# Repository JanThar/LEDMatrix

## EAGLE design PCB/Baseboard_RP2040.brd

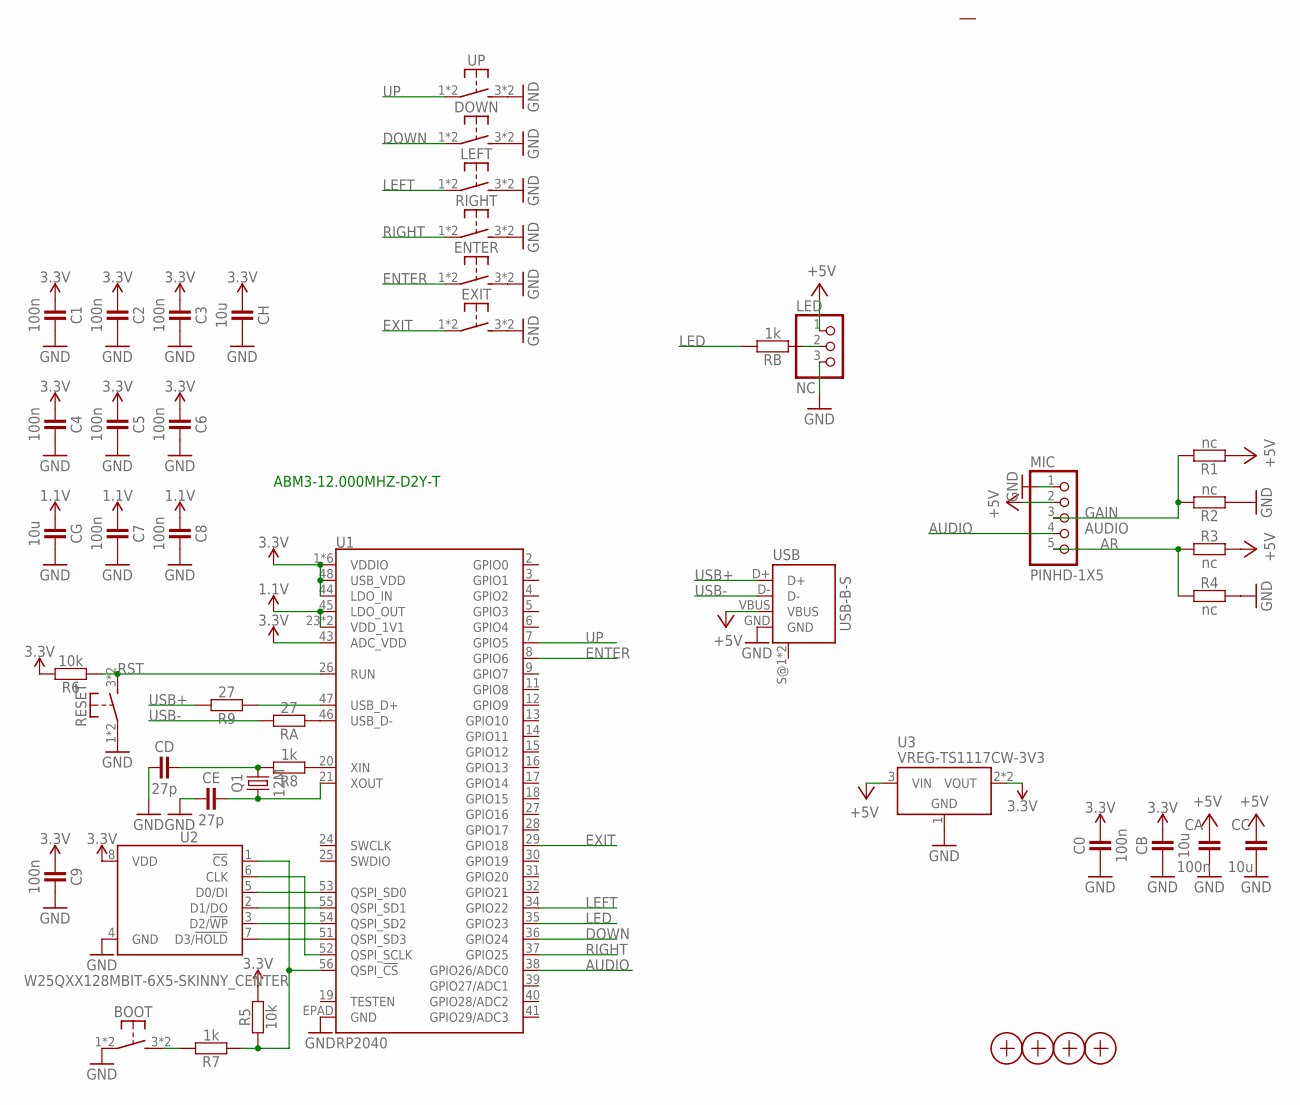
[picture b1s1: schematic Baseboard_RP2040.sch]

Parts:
BOOT: SW-TACTILE-6X6_SMD; SW6X6_SMD
C0, C1, C2, C3, C4, C5, C6, C7, C8, C9: 100n; C0603
CA: 100n; C0603
CB: 10u; C0603
CC: 10u; C0603
CD: 27p; C0603
CE: 27p; C0603
CG: 10u; C0603
CH: 10u; C0603
DOWN: SW-TACTILE-6X6_SMD; SW6X6_SMD
ENTER: SW-TACTILE-6X6_SMD; SW6X6_SMD
EXIT: SW-TACTILE-6X6_SMD; SW6X6_SMD
LED: NC; 1X03
LEFT: SW-TACTILE-6X6_SMD; SW6X6_SMD
MIC: PINHD-1X5; 1X05
Q1: 12M; CRYSTAL_CC2
R1, R2, R3, R4: nc; C0603
R5, R6: 10k; C0603
R7, R8: 1k; C0603
R9: 27; C0603
RA: 27; C0603
RB: 1k; C0603
RESET: SW-TACTILE-6X6_SMD; SW6X6_SMD
RIGHT: SW-TACTILE-6X6_SMD; SW6X6_SMD
U1: RP2040; QFN-56
U2: W25QXX128MBIT-6X5-SKINNY_CENTER; WSON-8-6X5-SKINNY_CENTERPAD
U3: VREG-TS1117CW-3V3; SOT223
UP: SW-TACTILE-6X6_SMD; SW6X6_SMD
USB: USB-B-S
X1, X2, X3, X4: PASSER-07; PASSER_07MM

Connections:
1.1V: C7.1, C8.1, CG.1, U1.23 (VDD_1V1), U1.45 (LDO_OUT), U1.50 (VDD_1V1)
3.3V: C0.2, C1.1, C2.1, C3.1, C4.1, C5.1, C6.1, C9.1, CB.2, CH.1, R5.2, R6.2, U1.1 (VDDIO), U1.10 (VDDIO), U1.22 (VDDIO), U1.33 (VDDIO), U1.42 (VDDIO), U1.43 (ADC_VDD), U1.44 (LDO_IN), U1.48 (USB_VDD), U1.49 (VDDIO), U2.8 (VDD), U3.2 (VOUT), U3.4 (VOUT)
+5V: CA.2, CC.2, LED.1, MIC.2, R1.1, R3.2, U3.3 (VIN), USB.VBUS
AR: MIC.5, R3.1, R4.1
AUDIO: MIC.4, U1.38 (GPIO26/ADC0)
DOWN: DOWN.1, DOWN.2 (P1), U1.36 (GPIO24)
ENTER: ENTER.1, ENTER.2 (P1), U1.8 (GPIO6)
EXIT: EXIT.1, EXIT.2 (P1), U1.29 (GPIO18)
GAIN: MIC.3, R1.2, R2.2
GND: BOOT.1, BOOT.2 (P1), C0.1, C1.2, C2.2, C3.2, C4.2, C5.2, C6.2, C7.2, C8.2, C9.2, CA.1, CB.1, CC.1, CD.1, CE.1, CG.2, CH.2, DOWN.3 (S1), DOWN.4 (S1), ENTER.3 (S1), ENTER.4 (S1), EXIT.3 (S1), EXIT.4 (S1), LED.3, LEFT.3 (S1), LEFT.4 (S1), MIC.1, R2.1, R4.2, RESET.1, RESET.2 (P1), RIGHT.3 (S1), RIGHT.4 (S1), U1.EPAD (GND), U2.4 (GND), U3.1 (GND), UP.3 (S1), UP.4 (S1), USB.GND
LED: RB.2, U1.35 (GPIO23)
LEFT: LEFT.1, LEFT.2 (P1), U1.34 (GPIO22)
unnamed: LED.2, RB.1
unnamed: U1.53 (QSPI_SD0), U2.5 (D0/DI)
unnamed: U1.55 (QSPI_SD1), U2.2 (D1/DO)
unnamed: U1.54 (QSPI_SD2), U2.3 (D2/!WP!)
unnamed: U1.51 (QSPI_SD3), U2.7 (D3/!HOLD!)
unnamed: U1.52 (QSPI_SCLK), U2.6 (CLK)
unnamed: R5.1, R7.1, U1.56 (QSPI_!CS!), U2.1 (!CS!)
unnamed: BOOT.3 (S1), BOOT.4 (S1), R7.2
unnamed: R8.1, U1.20 (XIN)
unnamed: CD.2, Q1.2, R8.2
unnamed: CE.2, Q1.1, U1.21 (XOUT)
unnamed: R9.1, U1.47 (USB_D+)
unnamed: RA.1, U1.46 (USB_D-)
RIGHT: RIGHT.1, RIGHT.2 (P1), U1.37 (GPIO25)
RST: R6.1, RESET.3 (S1), RESET.4 (S1), U1.26 (RUN)
UP: U1.7 (GPIO5), UP.1, UP.2 (P1)
USB+: R9.2, USB.D+
USB-: RA.2, USB.D-

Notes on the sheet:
ABM3-12.000MHZ-D2Y-T

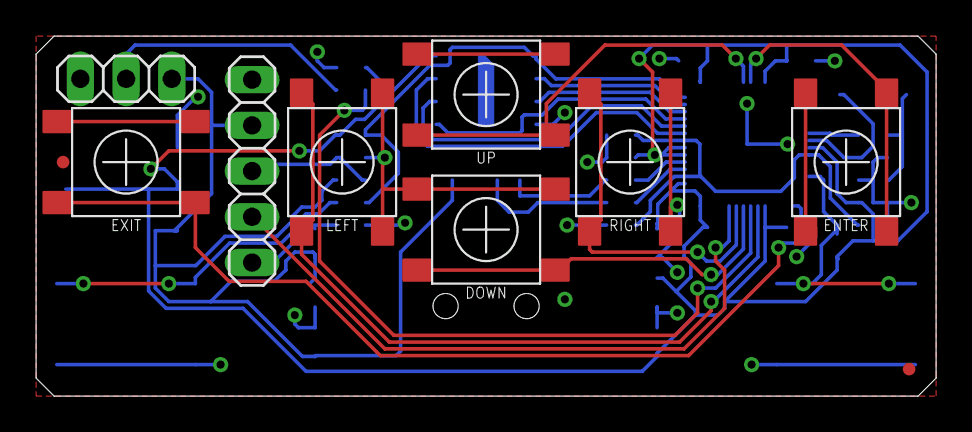
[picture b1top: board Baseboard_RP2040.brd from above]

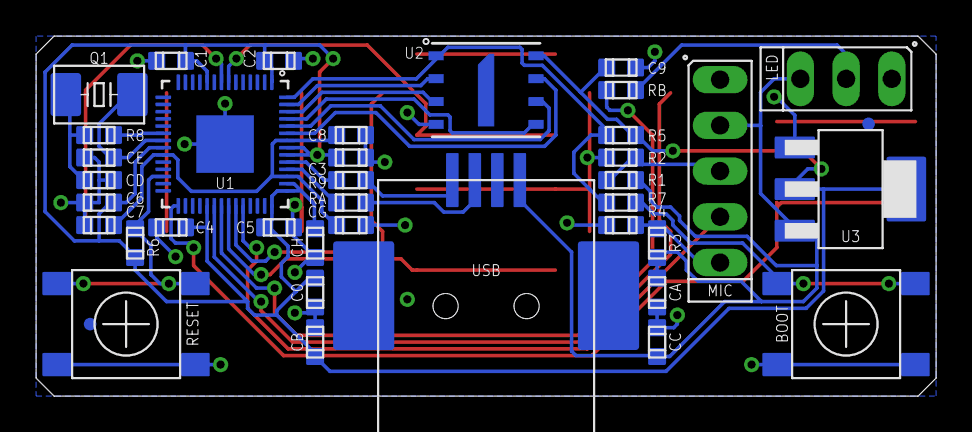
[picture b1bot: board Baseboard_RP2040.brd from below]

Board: 2 copper layers, 50.0 x 20.0 mm, 47 parts (37 on the bottom side), 30 nets.

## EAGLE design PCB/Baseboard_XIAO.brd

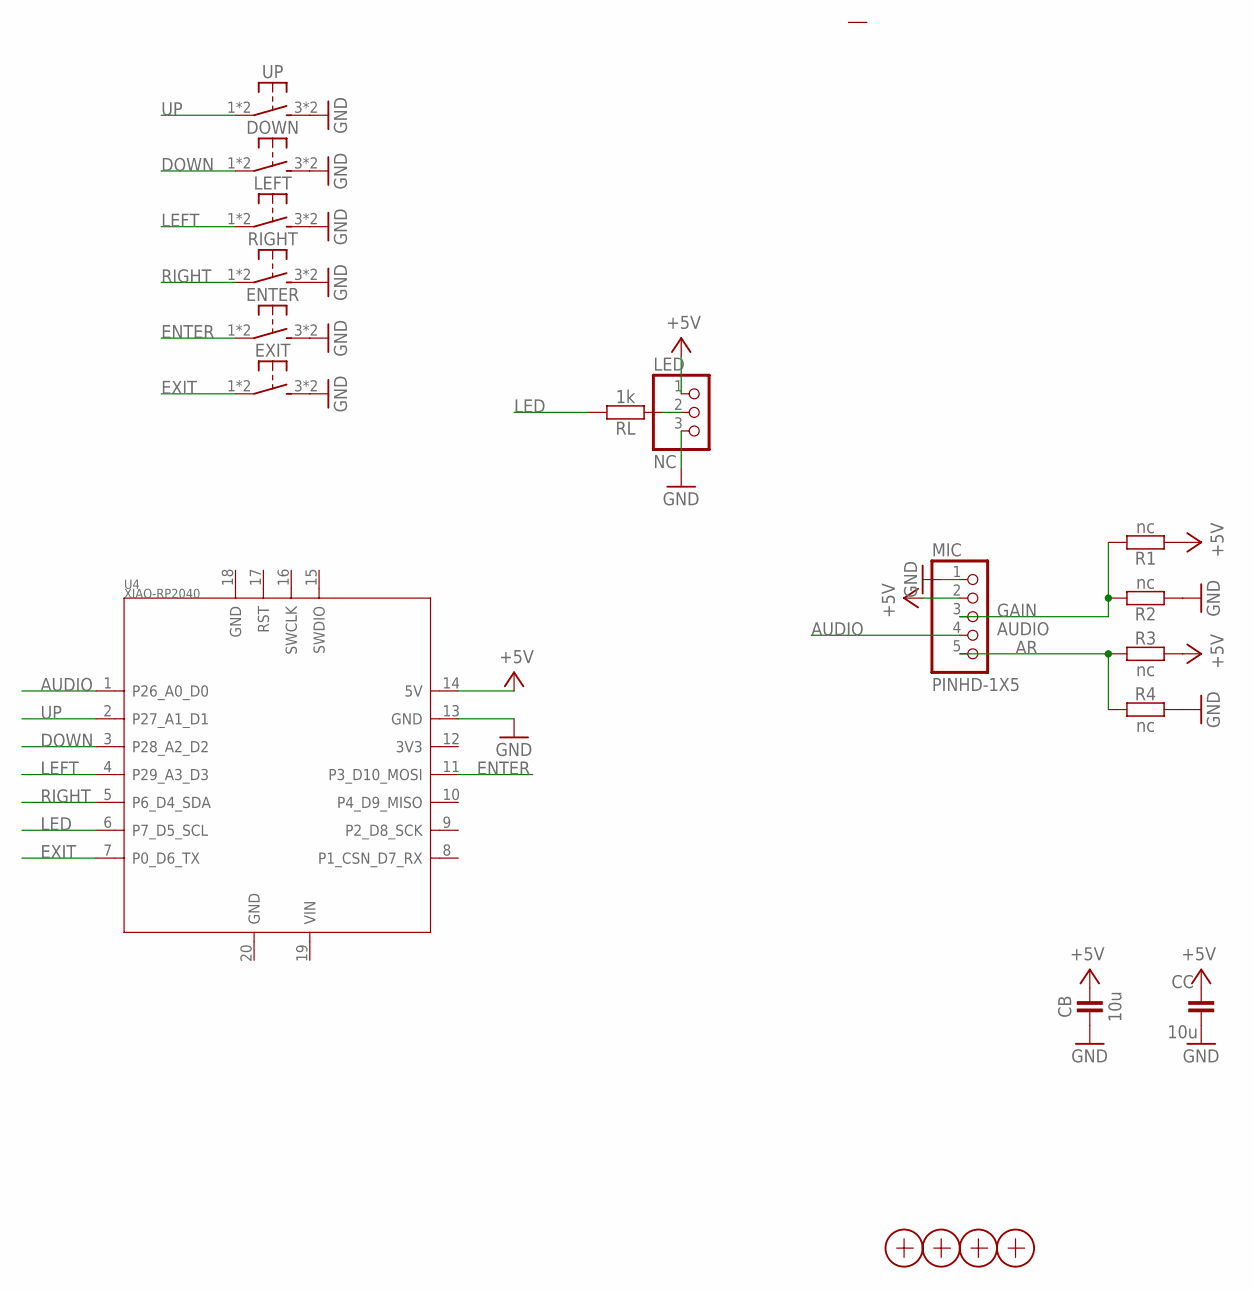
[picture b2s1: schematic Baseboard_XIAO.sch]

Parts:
CB: 10u; C0603
CC: 10u; C0603
DOWN: SW-TACTILELSH; SW6XG_LSH
ENTER: SW-TACTILELSH; SW6XG_LSH
EXIT: SW-TACTILELSH; SW6XG_LSH
LED: NC; 1X03
LEFT: SW-TACTILELSH; SW6XG_LSH
MIC: PINHD-1X5; 1X05
R1, R2, R3, R4: nc; C0603
RIGHT: SW-TACTILELSH; SW6XG_LSH
RL: 1k; C0603
U4: XIAO-RP2040; XIAO-SAMD21/RP2040-MODULE14P-2.54-21X17.8MM
UP: SW-TACTILELSH; SW6XG_LSH
X1, X2, X3, X4: PASSER-07; PASSER_07MM

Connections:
+5V: CB.2, CC.2, LED.1, MIC.2, R1.1, R3.2, U4.14 (5V)
AR: MIC.5, R3.1, R4.1
AUDIO: MIC.4, U4.1 (P26_A0_D0)
DOWN: DOWN.1, DOWN.2 (P1), U4.3 (P28_A2_D2)
ENTER: ENTER.1, ENTER.2 (P1), U4.11 (P3_D10_MOSI)
EXIT: EXIT.1, EXIT.2 (P1), U4.7 (P0_D6_TX)
GAIN: MIC.3, R1.2, R2.2
GND: CB.1, CC.1, DOWN.3 (S1), DOWN.4 (S1), ENTER.3 (S1), ENTER.4 (S1), EXIT.3 (S1), EXIT.4 (S1), LED.3, LEFT.3 (S1), LEFT.4 (S1), MIC.1, R2.1, R4.2, RIGHT.3 (S1), RIGHT.4 (S1), U4.13 (GND), UP.3 (S1), UP.4 (S1)
LED: RL.2, U4.6 (P7_D5_SCL)
LEFT: LEFT.1, LEFT.2 (P1), U4.4 (P29_A3_D3)
unnamed: LED.2, RL.1
RIGHT: RIGHT.1, RIGHT.2 (P1), U4.5 (P6_D4_SDA)
UP: U4.2 (P27_A1_D1), UP.1, UP.2 (P1)

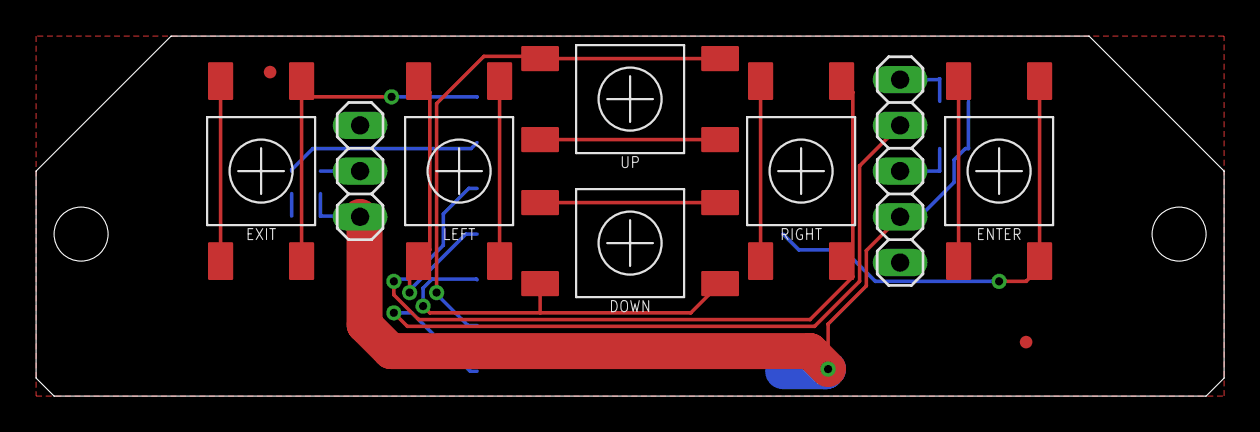
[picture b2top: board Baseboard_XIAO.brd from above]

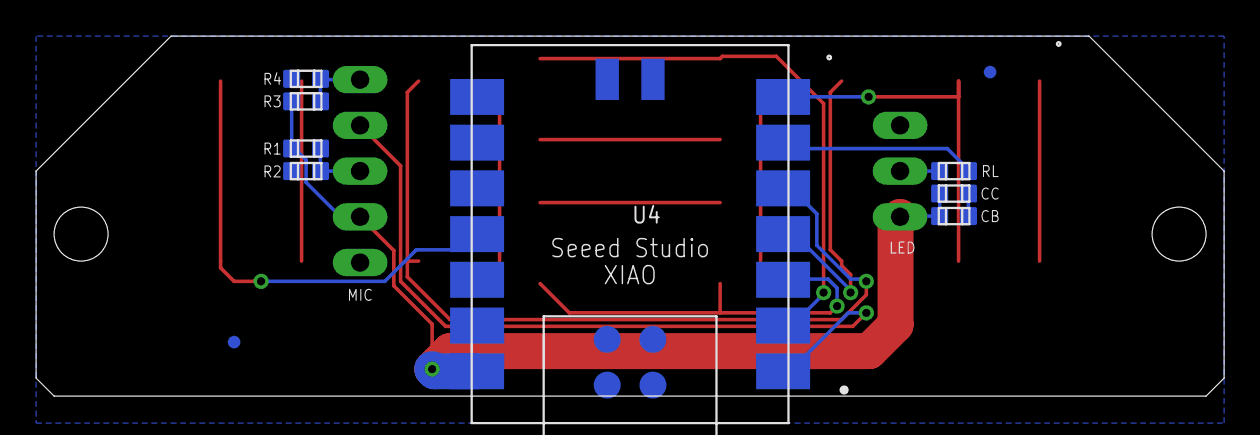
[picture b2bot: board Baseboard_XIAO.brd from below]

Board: 2 copper layers, 66.0 x 20.0 mm, 20 parts (10 on the bottom side), 13 nets.

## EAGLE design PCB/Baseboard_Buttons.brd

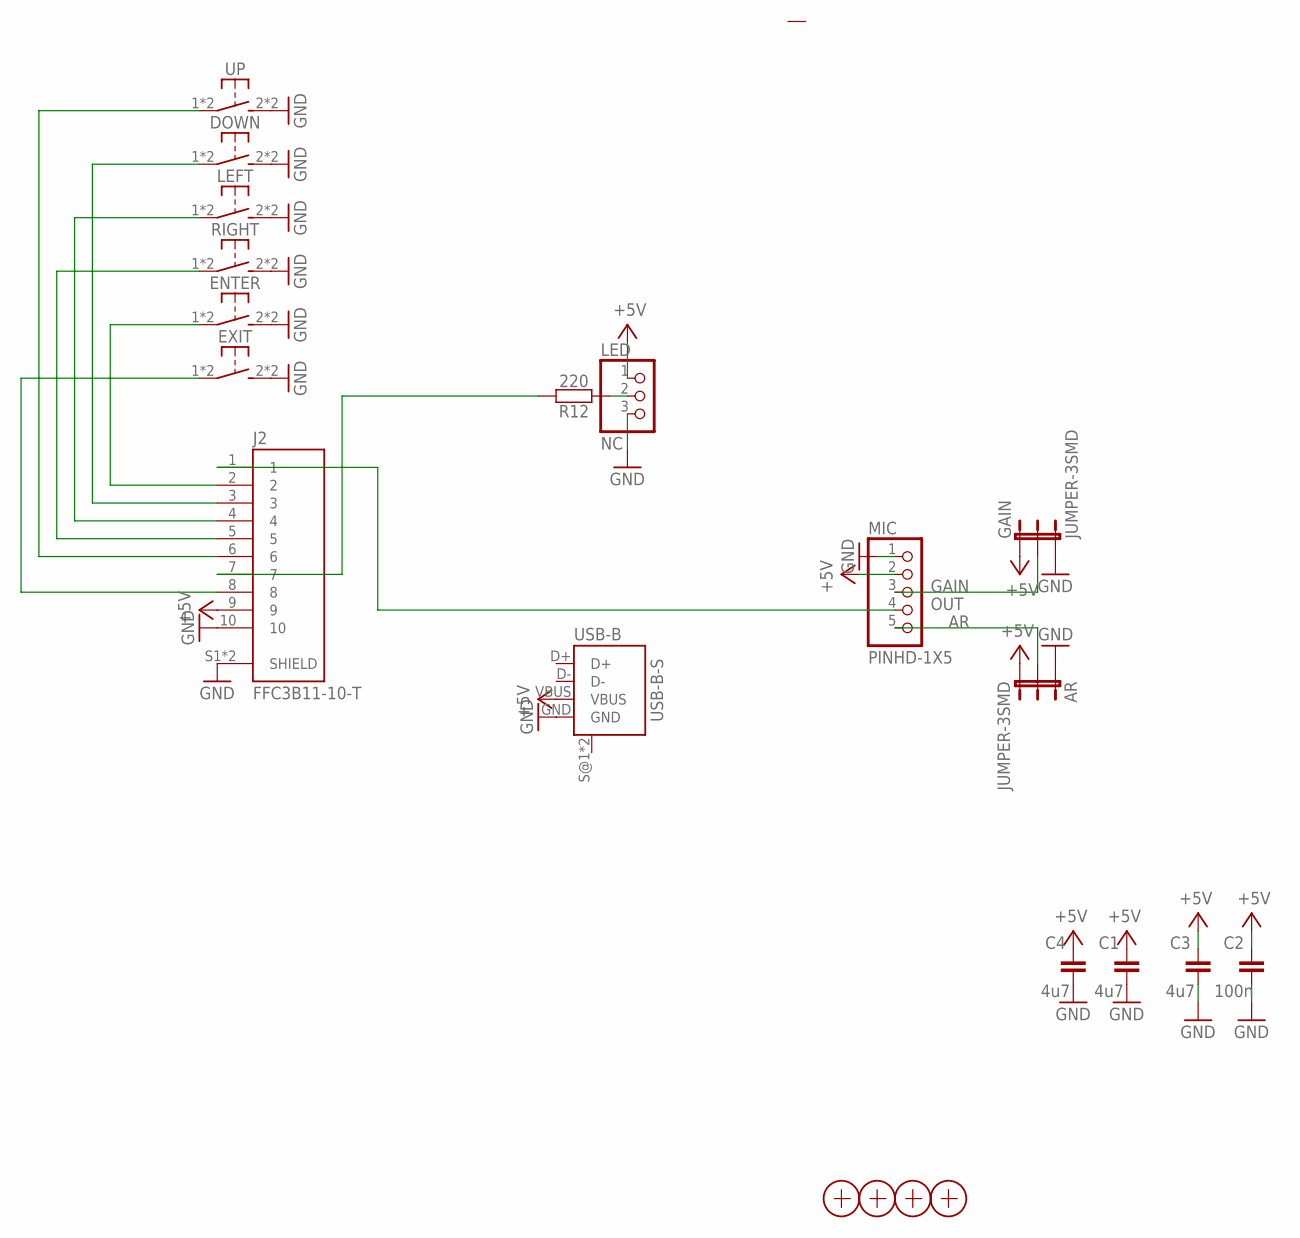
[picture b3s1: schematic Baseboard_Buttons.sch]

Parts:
AR: JUMPER-3SMD; SJ_3
C1, C3, C4: 4u7; C0805
C2: 100n; C0805
DOWN: SW-TACTILE-TL3305; TL3305
ENTER: SW-TACTILE-TL3305; TL3305
EXIT: SW-TACTILE-TL3305; TL3305
GAIN: JUMPER-3SMD; SJ_3
J2: FFC3B11-10-T; GCT_FFC3B11-10-T
LED: NC; 1X03
LEFT: SW-TACTILE-TL3305; TL3305
MIC: PINHD-1X5; 1X05
R12: 220; C0805
RIGHT: SW-TACTILE-TL3305; TL3305
UP: SW-TACTILE-TL3305; TL3305
USB-B: USB-B-S
X1, X2, X3, X4: PASSER-07; PASSER_07MM

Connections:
+5V: AR.3, C1.2, C2.2, C3.2, C4.2, GAIN.1, J2.9, LED.1, MIC.2, USB-B.VBUS
AR: AR.2, MIC.5
GAIN: GAIN.2, MIC.3
GND: AR.1, C1.1, C2.1, C3.1, C4.1, DOWN.2 (S1), DOWN.3 (S1), ENTER.2 (S1), ENTER.3 (S1), EXIT.2 (S1), EXIT.3 (S1), GAIN.3, J2.10, J2.S1 (SHIELD), J2.S2 (SHIELD), LED.3, LEFT.2 (S1), LEFT.3 (S1), MIC.1, RIGHT.2 (S1), RIGHT.3 (S1), UP.2 (S1), UP.3 (S1), USB-B.GND
unnamed: EXIT.1, EXIT.4 (P1), J2.8
unnamed: J2.4, LEFT.1, LEFT.4 (P1)
unnamed: J2.6, UP.1, UP.4 (P1)
unnamed: DOWN.1, DOWN.4 (P1), J2.3
unnamed: J2.5, RIGHT.1, RIGHT.4 (P1)
unnamed: ENTER.1, ENTER.4 (P1), J2.2
unnamed: J2.7, R12.2
unnamed: LED.2, R12.1
OUT: J2.1, MIC.4

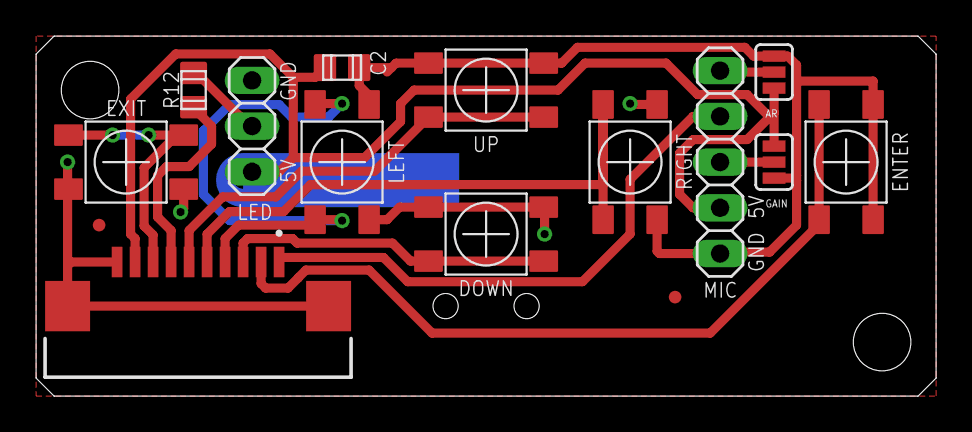
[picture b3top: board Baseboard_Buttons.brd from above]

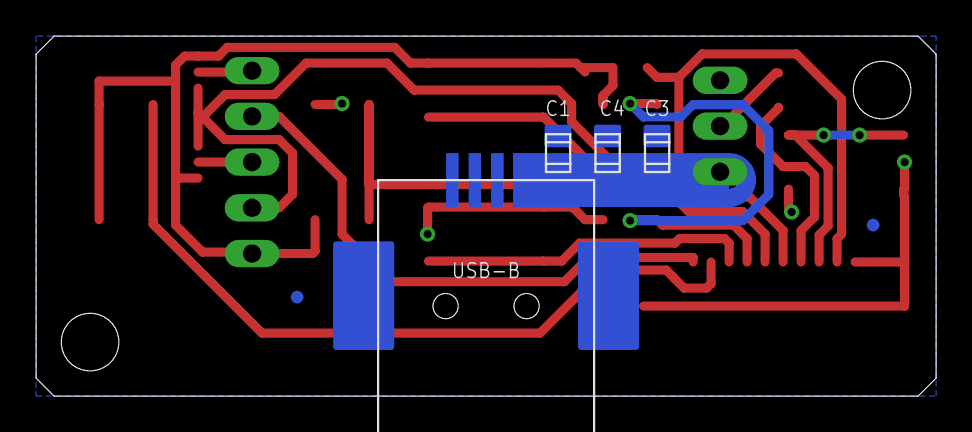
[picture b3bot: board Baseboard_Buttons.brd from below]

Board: 2 copper layers, 50.0 x 20.0 mm, 21 parts (6 on the bottom side), 13 nets.

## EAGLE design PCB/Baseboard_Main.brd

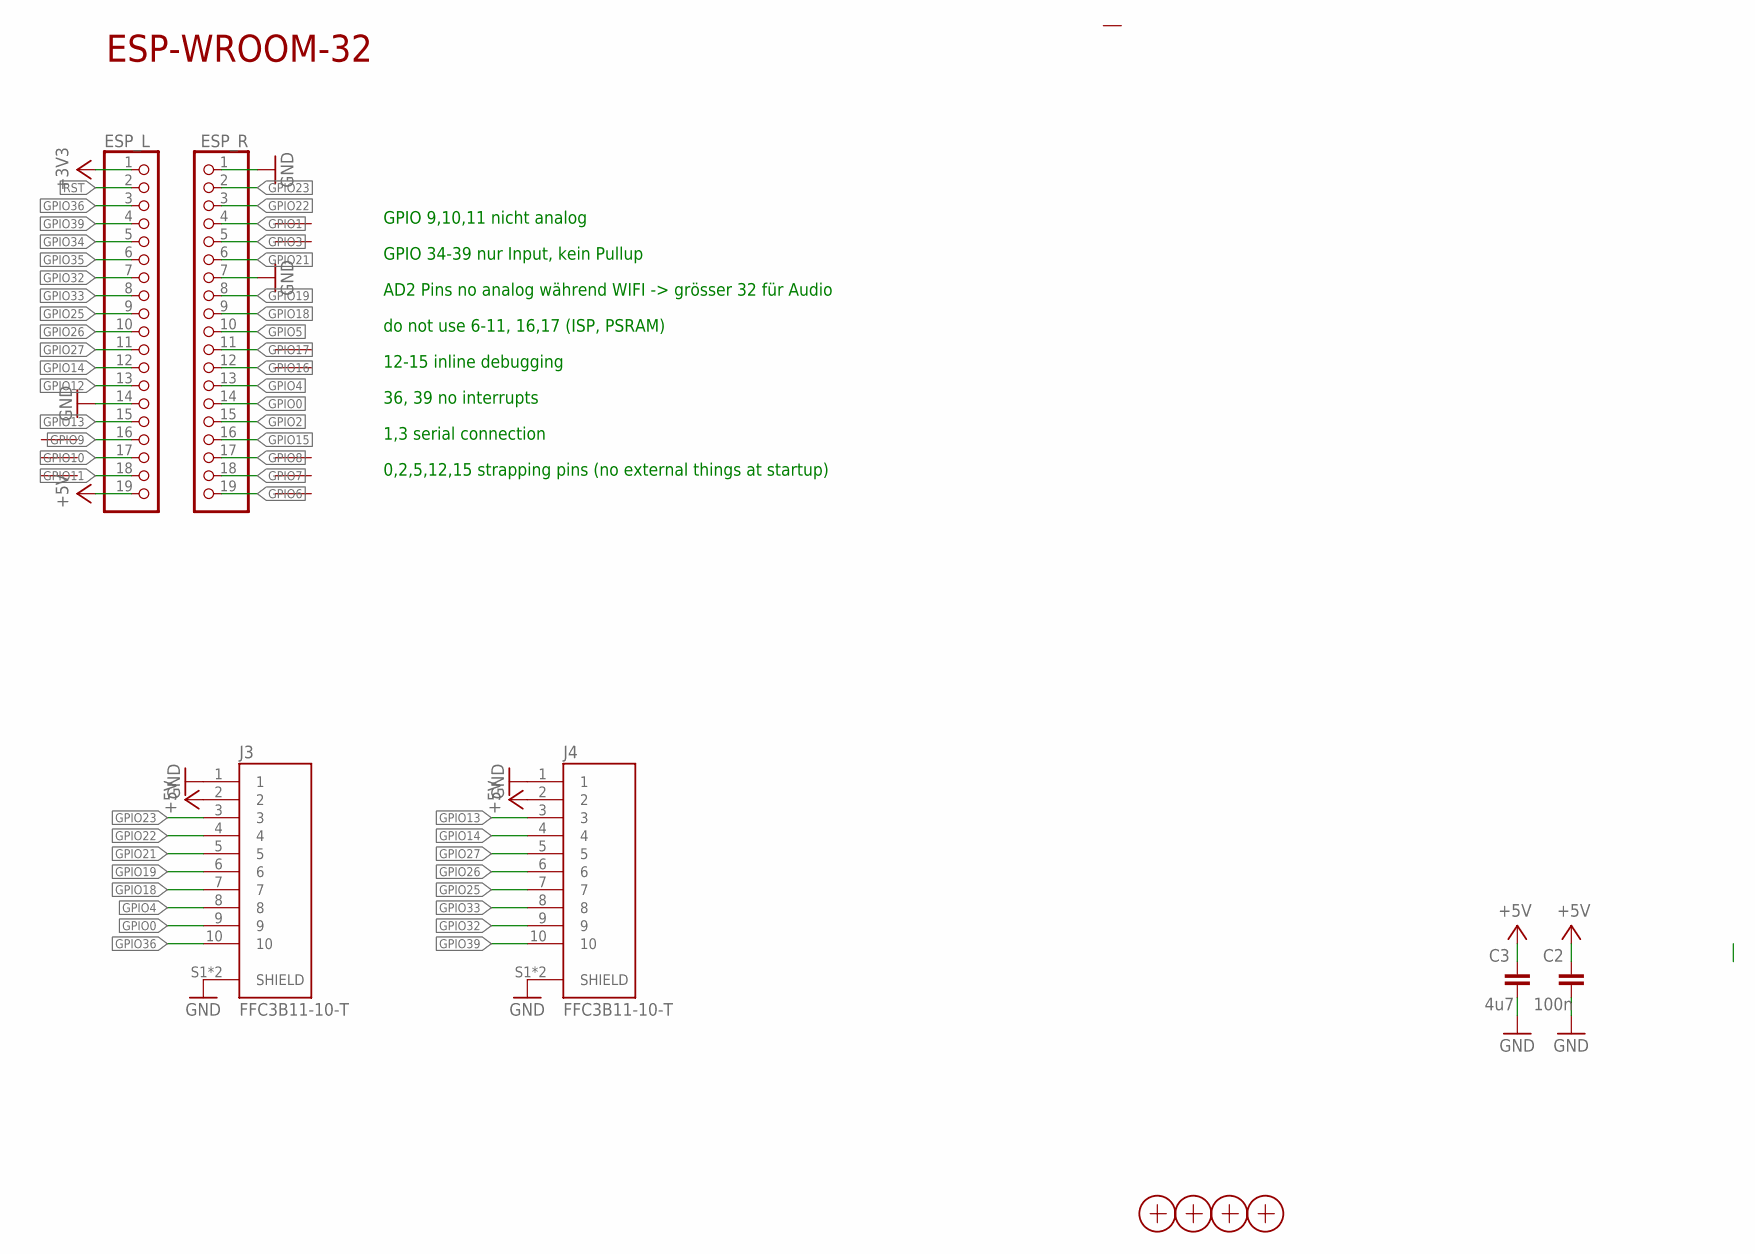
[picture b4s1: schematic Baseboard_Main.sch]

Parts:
C2: 100n; C0805
C3: 4u7; C0805
ESP_L: PINHD-1X19; 1X19
ESP_R: PINHD-1X19; 1X19
J3, J4: FFC3B11-10-T; GCT_FFC3B11-10-T
X1, X2, X3, X4: PASSER-07; PASSER_07MM

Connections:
+3V3: ESP_L.1
+5V: C2.2, C3.2, ESP_L.19, J3.2, J4.2
GND: C2.1, C3.1, ESP_L.14, ESP_R.1, ESP_R.7, J3.1, J3.S1 (SHIELD), J3.S2 (SHIELD), J4.1, J4.S1 (SHIELD), J4.S2 (SHIELD)
GPIO0: ESP_R.14, J3.9
GPIO1: ESP_R.4
GPIO2: ESP_R.15
GPIO3: ESP_R.5
GPIO4: ESP_R.13, J3.8
GPIO5: ESP_R.10
GPIO6: ESP_R.19
GPIO7: ESP_R.18
GPIO8: ESP_R.17
GPIO9: ESP_L.16
GPIO10: ESP_L.17
GPIO11: ESP_L.18
GPIO12: ESP_L.13
GPIO13: ESP_L.15, J4.3
GPIO14: ESP_L.12, J4.4
GPIO15: ESP_R.16
GPIO16: ESP_R.12
GPIO17: ESP_R.11
GPIO18: ESP_R.9, J3.7
GPIO19: ESP_R.8, J3.6
GPIO21: ESP_R.6, J3.5
GPIO22: ESP_R.3, J3.4
GPIO23: ESP_R.2, J3.3
GPIO25: ESP_L.9, J4.7
GPIO26: ESP_L.10, J4.6
GPIO27: ESP_L.11, J4.5
GPIO32: ESP_L.7, J4.9
GPIO33: ESP_L.8, J4.8
GPIO34: ESP_L.5
GPIO35: ESP_L.6
GPIO36: ESP_L.3, J3.10
GPIO39: ESP_L.4, J4.10
RST: ESP_L.2

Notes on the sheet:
ESP-WROOM-32
GPIO 9,10,11 nicht analog
GPIO 34-39 nur Input, kein Pullup
AD2 Pins no analog während WIFI -> grösser 32 für Audio
do not use 6-11, 16,17 (ISP, PSRAM)
12-15 inline debugging
36, 39 no interrupts
1,3 serial connection
0,2,5,12,15 strapping pins (no external things at startup)

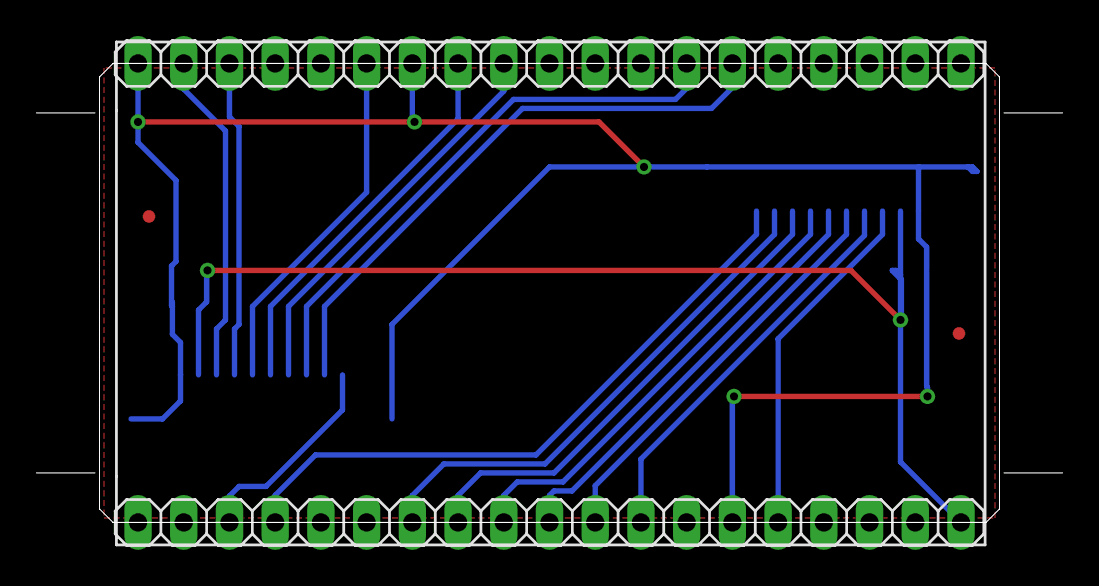
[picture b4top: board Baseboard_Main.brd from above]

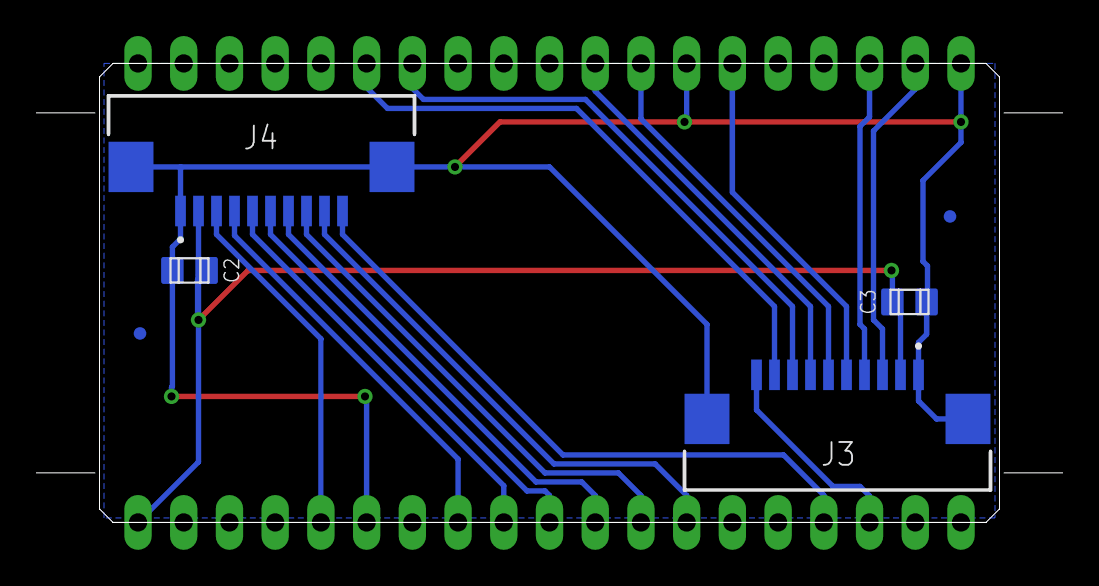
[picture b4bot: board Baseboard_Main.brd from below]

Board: 2 copper layers, 50.0 x 25.5 mm, 10 parts (6 on the bottom side), 18 nets.

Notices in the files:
parts and their libraries:
SparkFun-Retired: Licensing: Creative Commons ShareAlike 4.0 International - https://creativecommons.org/licenses/by-sa/4.0
